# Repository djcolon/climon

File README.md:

# cliMon

**Daniel Colon - 23/03/2025**

An ESP32 that reads temperature, humidity and pressure using a che BME-280 clone.
Connects to wifi and makes sensor data available as JSON on a http call.

Built with an ESP32-C3 Mini, which I bought for £1.83
[here.](https://www.aliexpress.com/item/1005005967641936.html)

And a BME-280-3.3 which is £2.69
[here.](https://www.aliexpress.com/item/1005006221391170.html)

[Built using PlatformIO](https://platformio.org/)

## Testing

To run tests you need to have configured the platformIO native environment.
See the [platformIO guides](https://piolabs.com/blog/insights/unit-testing-part-1.html)
for more detail.

After installation, run tests by navigating to `native > advanced > test` in the
platformIO sidebar.

## Images

The devboard pinout.

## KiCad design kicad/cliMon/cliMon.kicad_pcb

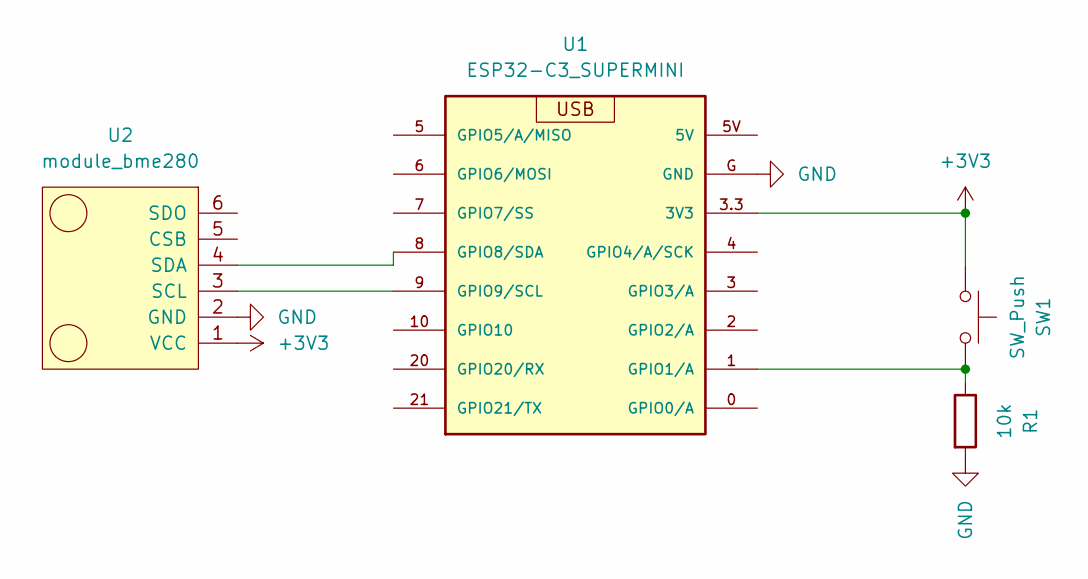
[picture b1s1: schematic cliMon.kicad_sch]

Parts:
R1: 10k; R_Axial_DIN0207_L6.3mm_D2.5mm_P10.16mm_Horizontal
SW1: SW_Push; SW_PUSH_6mm_H5mm
U1: ESP32-C3_SUPERMINI; MODULE_ESP32-C3_SUPERMINI
U2: module_bme280

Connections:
+3V3: SW1.1, U1.3.3 (3V3), U2.1 (VCC)
GND: R1.2, U1.G (GND), U2.2 (GND)
unnamed: R1.1, SW1.2, U1.1 (GPIO1/A)
unnamed: U1.8 (GPIO8/SDA), U2.4 (SDA)
unnamed: U1.9 (GPIO9/SCL), U2.3 (SCL)

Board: 2 copper layers, 4 parts (0 on the bottom side), 5 nets, no tracks yet.

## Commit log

2026-02-08 Bugfixes for async captive portal.
2026-02-08 Cleanup, changed sensor settings to reduce self-heating.
2026-02-08 Bugfixes.
2026-02-09 More debugging, echoing out short commit hash as version.
2026-03-21 Little tidy
2026-06-22 Added CORS support.
2026-06-22 fixed cors
2026-06-22 Serving dashbaord app from spiffs.
